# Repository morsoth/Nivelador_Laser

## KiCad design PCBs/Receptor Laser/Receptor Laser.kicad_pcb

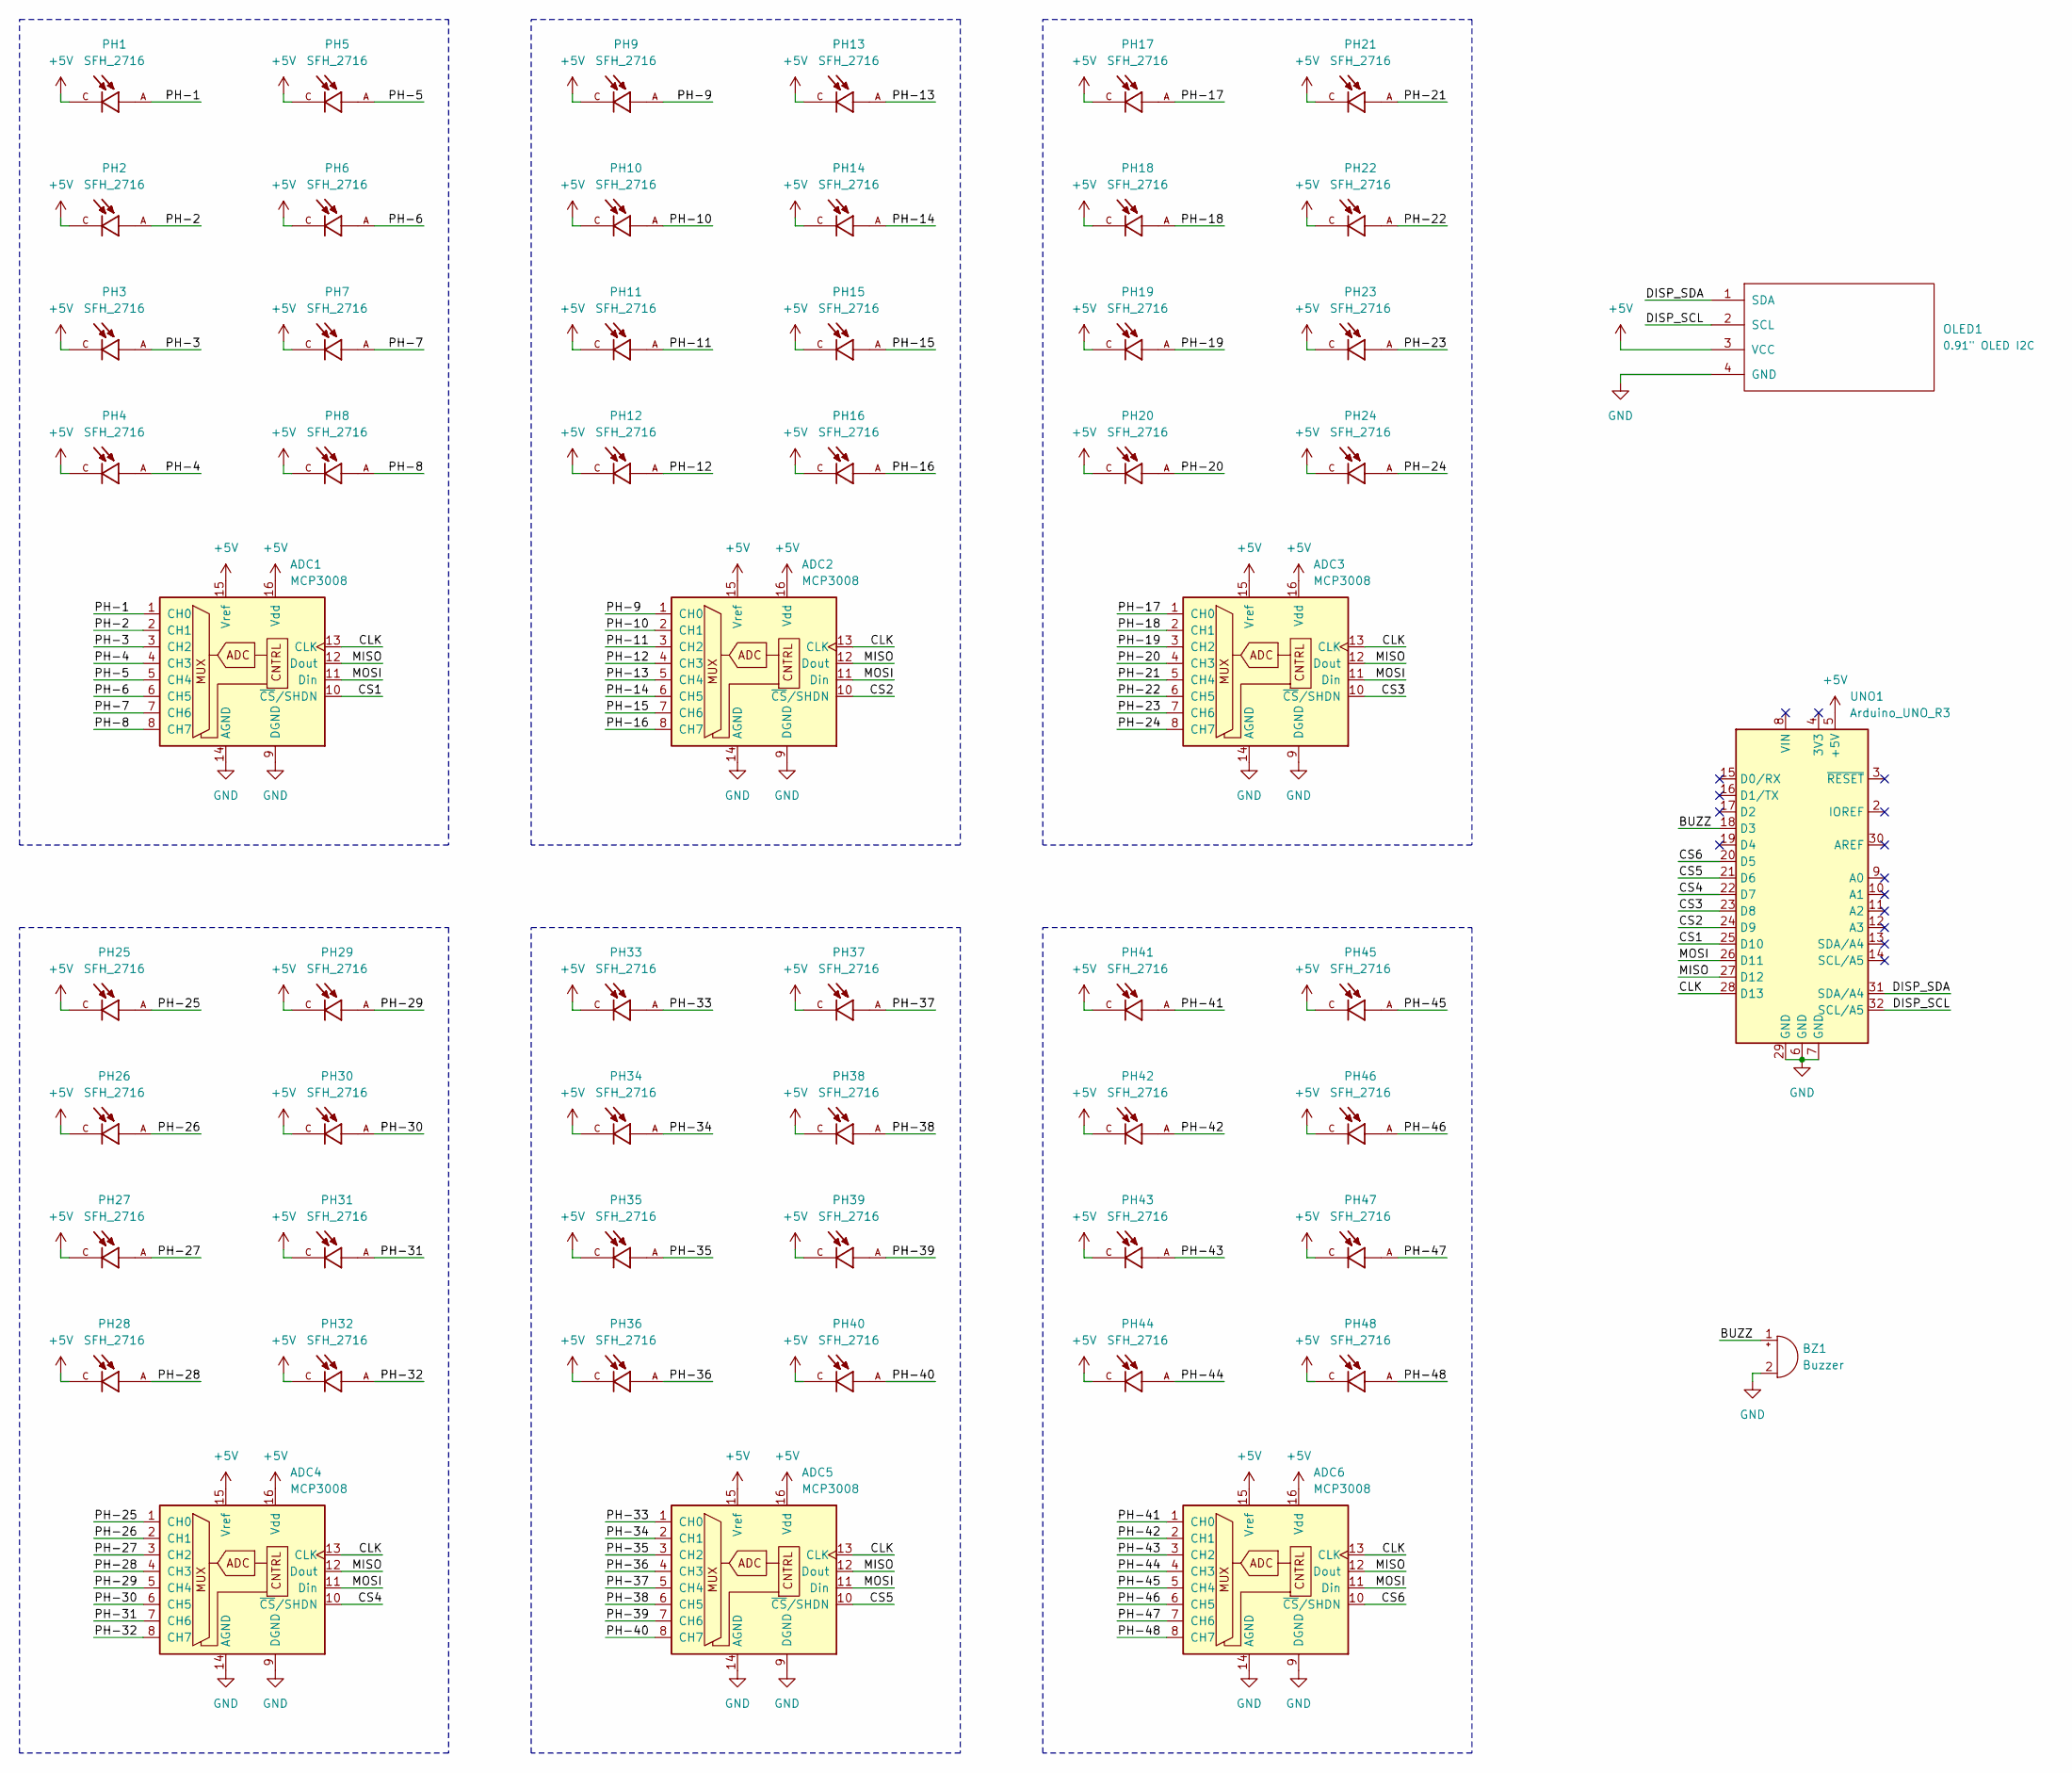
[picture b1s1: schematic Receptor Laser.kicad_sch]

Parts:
ADC1, ADC2, ADC3, ADC4, ADC5, ADC6: MCP3008; SOIC-16_3.9x9.9mm_P1.27mm
BZ1: Buzzer; Buzzer_12x9.5RM7.6
OLED1: 0.91" OLED I2C; OLED
PH1, PH2, PH3, PH4, PH5, PH6, PH7, PH8, PH9, PH10, PH11, PH12, PH13, PH14, PH15, PH16, PH17, PH18, PH19, PH20, PH21, PH22, PH23, PH24, PH25, PH26, PH27, PH28, PH29, PH30, PH31, PH32, PH33, PH34, PH35, PH36, PH37, PH38, PH39, PH40, PH41, PH42, PH43, PH44, PH45, PH46, PH47, PH48: SFH_2716; LEDC2012X100N; PARTREV 1.1
UNO1: Arduino_UNO_R3

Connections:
+5V: ADC1.15 (Vref), ADC1.16 (Vdd), ADC2.15 (Vref), ADC2.16 (Vdd), ADC3.15 (Vref), ADC3.16 (Vdd), ADC4.15 (Vref), ADC4.16 (Vdd), ADC5.15 (Vref), ADC5.16 (Vdd), ADC6.15 (Vref), ADC6.16 (Vdd), OLED1.3 (VCC), PH1.C, PH2.C, PH3.C, PH4.C, PH5.C, PH6.C, PH7.C, PH8.C, PH9.C, PH10.C, PH11.C, PH12.C, PH13.C, PH14.C, PH15.C, PH16.C, PH17.C, PH18.C, PH19.C, PH20.C, PH21.C, PH22.C, PH23.C, PH24.C, PH25.C, PH26.C, PH27.C, PH28.C, PH29.C, PH30.C, PH31.C, PH32.C, PH33.C, PH34.C, PH35.C, PH36.C, PH37.C, PH38.C, PH39.C, PH40.C, PH41.C, PH42.C, PH43.C, PH44.C, PH45.C, PH46.C, PH47.C, PH48.C, UNO1.5 (+5V)
/BUZZ: BZ1.1 (-), UNO1.18 (D3)
/CLK: ADC1.13 (CLK), ADC2.13 (CLK), ADC3.13 (CLK), ADC4.13 (CLK), ADC5.13 (CLK), ADC6.13 (CLK), UNO1.28 (D13)
/CS1: ADC1.10 (~CS/SHDN), UNO1.25 (D10)
/CS2: ADC2.10 (~CS/SHDN), UNO1.24 (D9)
/CS3: ADC3.10 (~CS/SHDN), UNO1.23 (D8)
/CS4: ADC4.10 (~CS/SHDN), UNO1.22 (D7)
/CS5: ADC5.10 (~CS/SHDN), UNO1.21 (D6)
/CS6: ADC6.10 (~CS/SHDN), UNO1.20 (D5)
/DISP_SCL: OLED1.2 (SCL), UNO1.32 (SCL/A5)
/DISP_SDA: OLED1.1 (SDA), UNO1.31 (SDA/A4)
/MISO: ADC1.12 (Dout), ADC2.12 (Dout), ADC3.12 (Dout), ADC4.12 (Dout), ADC5.12 (Dout), ADC6.12 (Dout), UNO1.27 (D12)
/MOSI: ADC1.11 (Din), ADC2.11 (Din), ADC3.11 (Din), ADC4.11 (Din), ADC5.11 (Din), ADC6.11 (Din), UNO1.26 (D11)
/PH-1: ADC1.1 (CH0), PH1.A
/PH-2: ADC1.2 (CH1), PH2.A
/PH-3: ADC1.3 (CH2), PH3.A
/PH-4: ADC1.4 (CH3), PH4.A
/PH-5: ADC1.5 (CH4), PH5.A
/PH-6: ADC1.6 (CH5), PH6.A
/PH-7: ADC1.7 (CH6), PH7.A
/PH-8: ADC1.8 (CH7), PH8.A
/PH-9: ADC2.1 (CH0), PH9.A
/PH-10: ADC2.2 (CH1), PH10.A
/PH-11: ADC2.3 (CH2), PH11.A
/PH-12: ADC2.4 (CH3), PH12.A
/PH-13: ADC2.5 (CH4), PH13.A
/PH-14: ADC2.6 (CH5), PH14.A
/PH-15: ADC2.7 (CH6), PH15.A
/PH-16: ADC2.8 (CH7), PH16.A
/PH-17: ADC3.1 (CH0), PH17.A
/PH-18: ADC3.2 (CH1), PH18.A
/PH-19: ADC3.3 (CH2), PH19.A
/PH-20: ADC3.4 (CH3), PH20.A
/PH-21: ADC3.5 (CH4), PH21.A
/PH-22: ADC3.6 (CH5), PH22.A
/PH-23: ADC3.7 (CH6), PH23.A
/PH-24: ADC3.8 (CH7), PH24.A
/PH-25: ADC4.1 (CH0), PH25.A
/PH-26: ADC4.2 (CH1), PH26.A
/PH-27: ADC4.3 (CH2), PH27.A
/PH-28: ADC4.4 (CH3), PH28.A
/PH-29: ADC4.5 (CH4), PH29.A
/PH-30: ADC4.6 (CH5), PH30.A
/PH-31: ADC4.7 (CH6), PH31.A
/PH-32: ADC4.8 (CH7), PH32.A
/PH-33: ADC5.1 (CH0), PH33.A
/PH-34: ADC5.2 (CH1), PH34.A
/PH-35: ADC5.3 (CH2), PH35.A
/PH-36: ADC5.4 (CH3), PH36.A
/PH-37: ADC5.5 (CH4), PH37.A
/PH-38: ADC5.6 (CH5), PH38.A
/PH-39: ADC5.7 (CH6), PH39.A
/PH-40: ADC5.8 (CH7), PH40.A
/PH-41: ADC6.1 (CH0), PH41.A
/PH-42: ADC6.2 (CH1), PH42.A
/PH-43: ADC6.3 (CH2), PH43.A
/PH-44: ADC6.4 (CH3), PH44.A
/PH-45: ADC6.5 (CH4), PH45.A
/PH-46: ADC6.6 (CH5), PH46.A
/PH-47: ADC6.7 (CH6), PH47.A
/PH-48: ADC6.8 (CH7), PH48.A
GND: ADC1.9 (DGND), ADC1.14 (AGND), ADC2.9 (DGND), ADC2.14 (AGND), ADC3.9 (DGND), ADC3.14 (AGND), ADC4.9 (DGND), ADC4.14 (AGND), ADC5.9 (DGND), ADC5.14 (AGND), ADC6.9 (DGND), ADC6.14 (AGND), BZ1.2 (+), OLED1.4 (GND), UNO1.6 (GND), UNO1.7 (GND), UNO1.29 (GND)

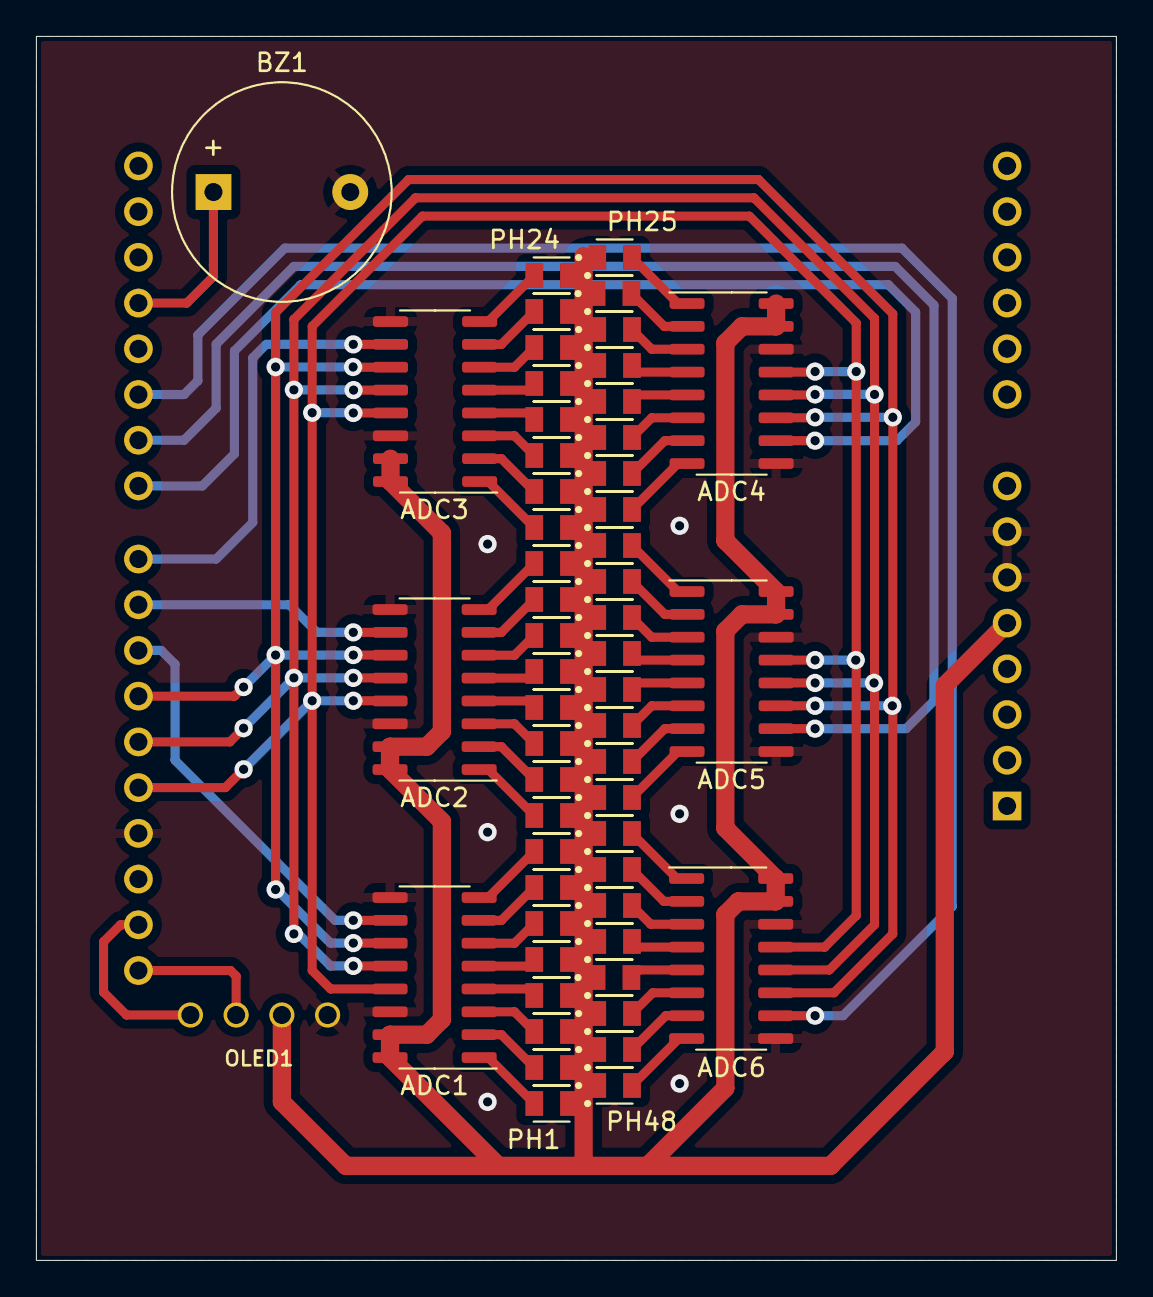
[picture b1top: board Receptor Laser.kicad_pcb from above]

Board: 2 copper layers, 60.0 x 68.0 mm, 57 parts (1 on the bottom side), 62 nets.

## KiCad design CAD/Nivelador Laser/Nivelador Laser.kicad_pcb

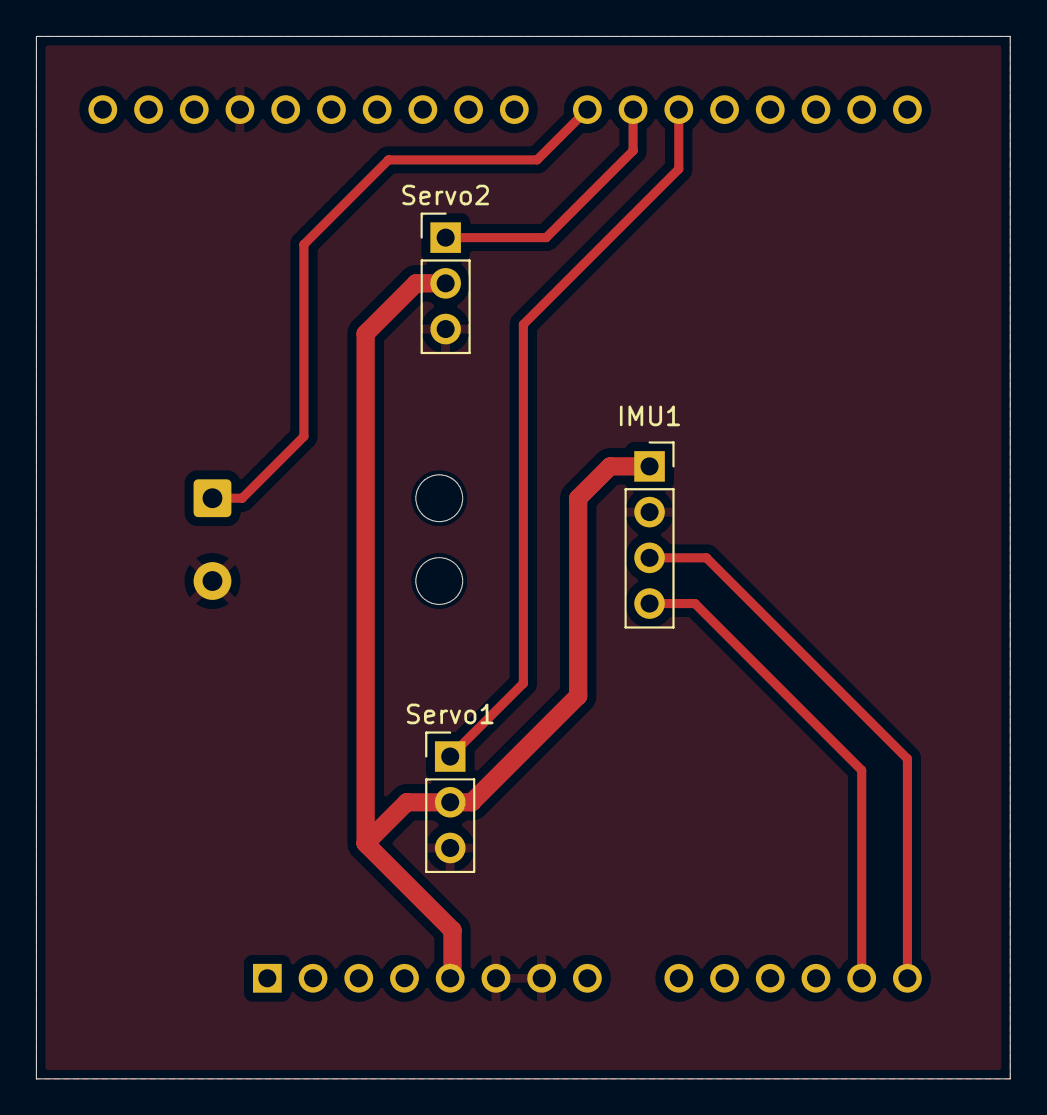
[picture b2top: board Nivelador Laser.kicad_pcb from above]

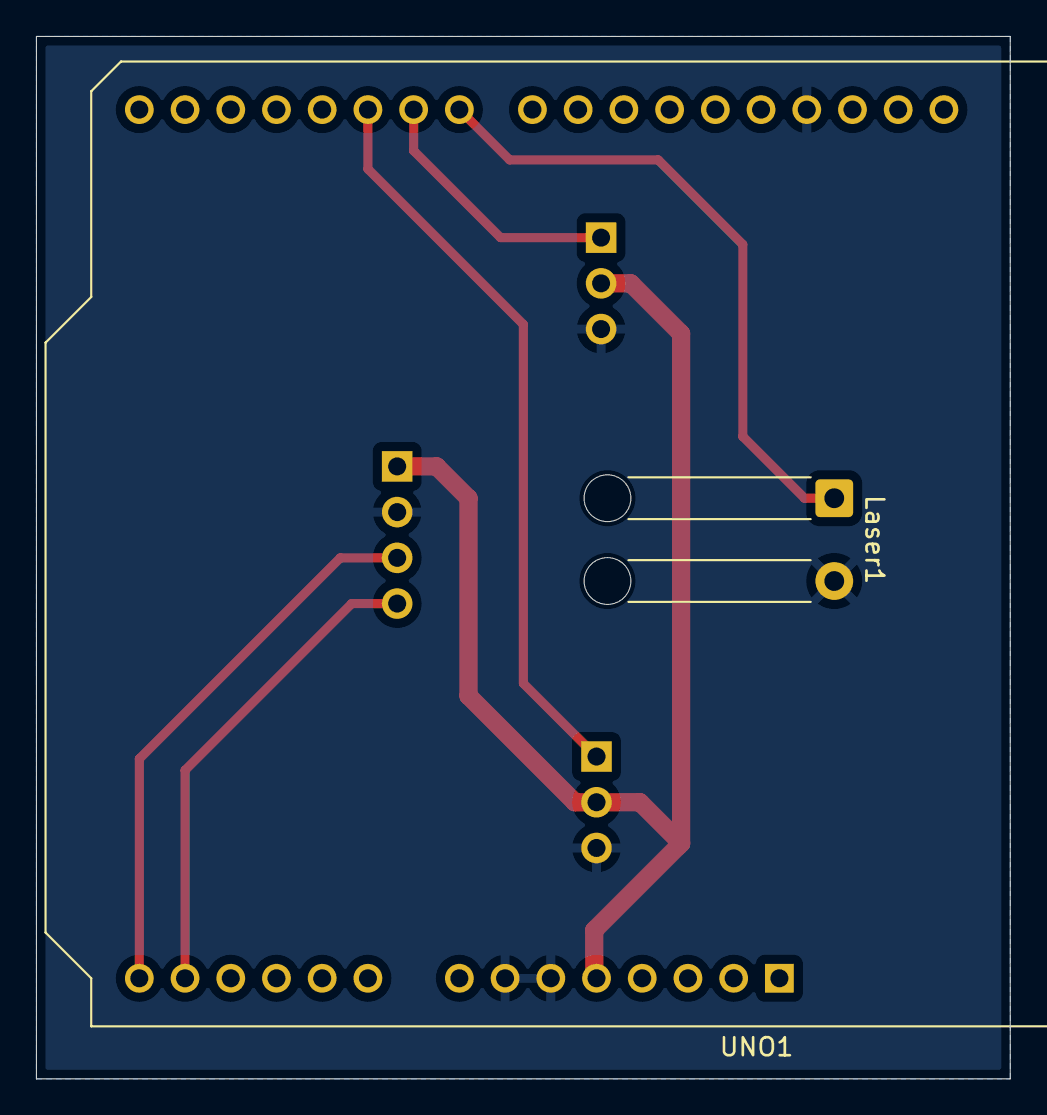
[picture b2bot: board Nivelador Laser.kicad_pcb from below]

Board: 2 copper layers, 54.1 x 57.9 mm, 5 parts (2 on the bottom side), 7 nets.

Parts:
IMU1: MPU-6050; PinSocket_1x04_P2.54mm_Vertical
Laser1: Laser_Diode; SolderWire-0.5sqmm_1x02_P4.6mm_D0.9mm_OD2.1mm_Relief
Servo1, Servo2: Motor_Servo; PinHeader_1x03_P2.54mm_Vertical
UNO1: Arduino_UNO_R3

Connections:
+5V: IMU1.1, Servo1.2 (+), Servo2.2 (+), UNO1.5 (+5V)
/IMU_SCL: IMU1.3, UNO1.14 (SCL/A5)
/IMU_SDA: IMU1.4, UNO1.13 (SDA/A4)
/LSR: Laser1.1, UNO1.22 (D7)
/SV1: Servo1.1 (PWM), UNO1.20 (D5)
/SV2: Servo2.1 (PWM), UNO1.21 (D6)
GND: IMU1.2, Laser1.2, Servo1.3 (-), Servo2.3 (-), UNO1.6 (GND), UNO1.7 (GND), UNO1.29 (GND)

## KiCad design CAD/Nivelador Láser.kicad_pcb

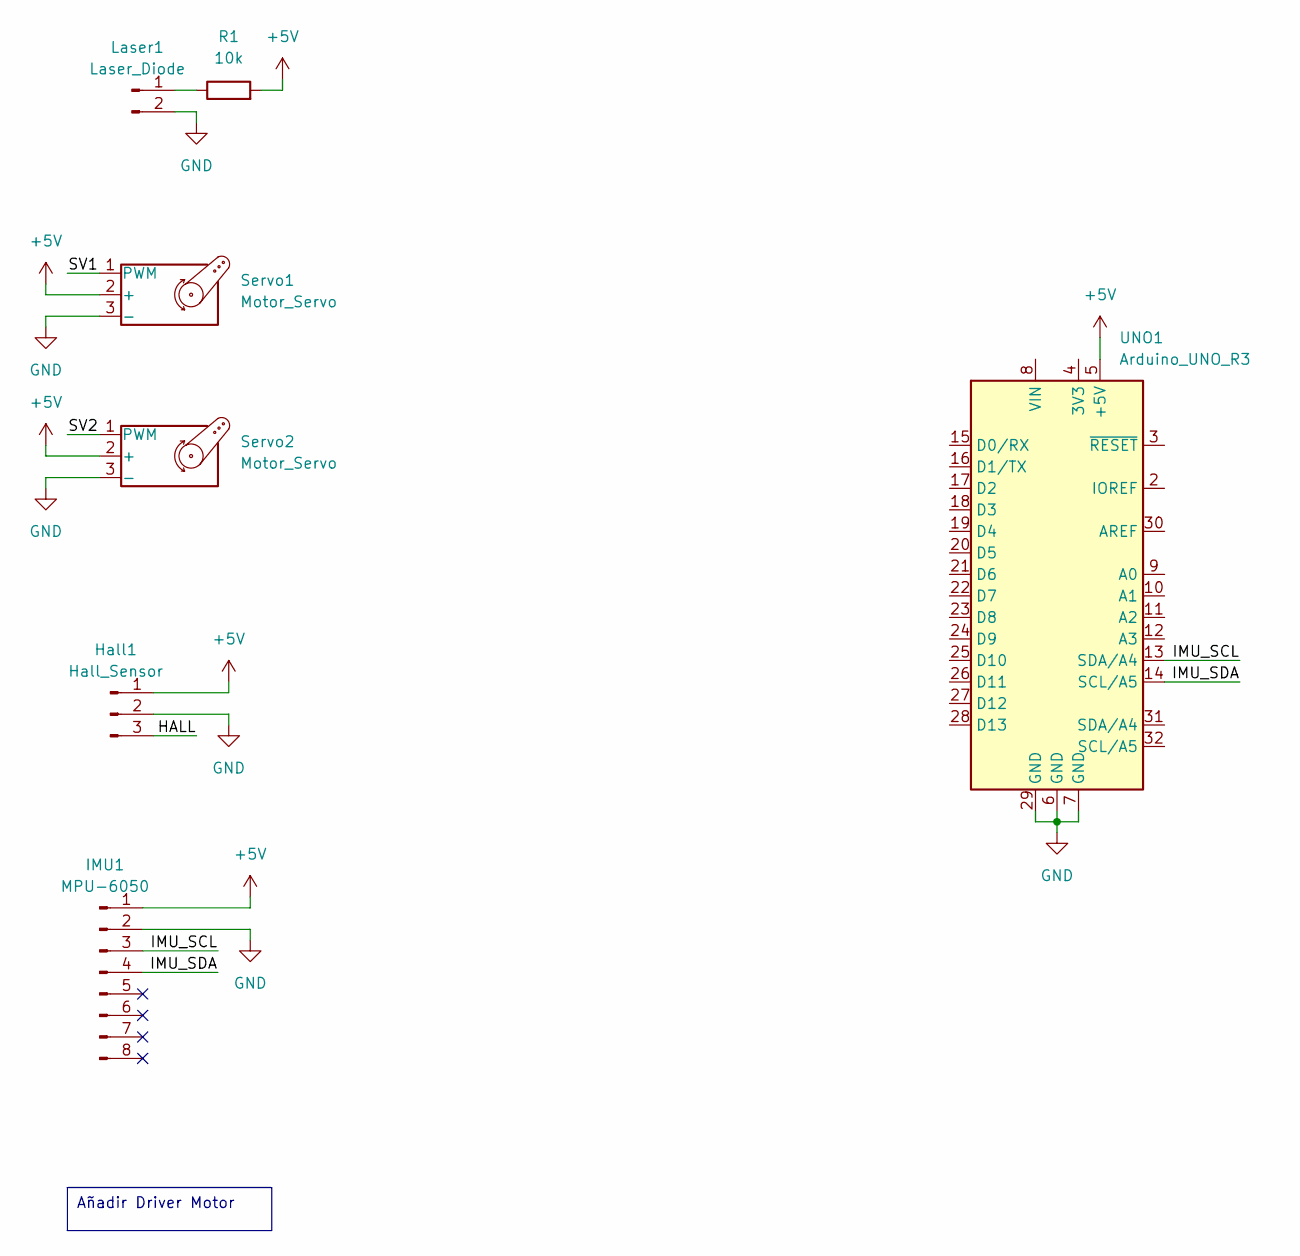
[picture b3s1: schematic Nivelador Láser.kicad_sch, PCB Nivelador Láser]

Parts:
Hall1: Hall_Sensor; SolderWire-0.5sqmm_1x03_P4.6mm_D0.9mm_OD2.1mm_Relief
IMU1: MPU-6050; PinSocket_1x08_P2.54mm_Vertical
Laser1: Laser_Diode; SolderWire-0.5sqmm_1x02_P4.6mm_D0.9mm_OD2.1mm_Relief
R1: 10k; R_0805_2012Metric_Pad1.20x1.40mm_HandSolder
Servo1, Servo2: Motor_Servo; PinHeader_1x03_P2.54mm_Vertical
UNO1: Arduino_UNO_R3

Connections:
+5V: Hall1.1, IMU1.1, R1.2, Servo1.2 (+), Servo2.2 (+), UNO1.5 (+5V)
/HALL: Hall1.3
/IMU_SCL: IMU1.3, UNO1.13 (SDA/A4)
/IMU_SDA: IMU1.4, UNO1.14 (SCL/A5)
/SV1: Servo1.1 (PWM)
/SV2: Servo2.1 (PWM)
GND: Hall1.2, IMU1.2, Laser1.2, Servo1.3 (-), Servo2.3 (-), UNO1.6 (GND), UNO1.7 (GND), UNO1.29 (GND)
unnamed: Laser1.1, R1.1

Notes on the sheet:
Añadir Driver Motor

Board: 2 copper layers, 7 parts (0 on the bottom side), 5 nets, no tracks yet.

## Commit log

2024-12-07 reset
2024-12-07 kicad files added
2024-12-07 added laser reciever
2024-12-07 added local cad libs
2024-12-07 added sumbols and footprints subfolders
2024-12-07 local paths libs
2024-12-07 gitignore kicad
2025-01-08 pcb receptor
2025-01-14 ignore .kicad_sch-bak
2025-01-21 receptor code
2025-01-29 organization
